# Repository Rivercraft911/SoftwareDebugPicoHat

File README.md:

# Software Debug Pico Hat

A simple breakout board for the Raspberry Pi Pico, designed for S-Band and UHF LORA modules. It also includes exposed gpio pins for connection to other boards within the Samwise avionics stack.

[View Schematic PDF](Plots/SoftwareDebugPicoHat.pdf)

## Power

//type this up later frfr

## Pinout

This board connects to a Raspberry Pi Pico and provides the following pinouts:

### Raspberry Pi Communication
| Pin | Function      | Pico Pin |
|-----|---------------|----------|
| 0   | RPI_TX        | GP0      |
| 1   | RPI_RX        | GP1      |
| 2   | RPI_ENABLE    | GP2      |
| 3   | RPI_RESET     | GP3      |

### ACDS Communication
| Pin | Function      | Pico Pin |
|-----|---------------|----------|
| 4   | ACDS_TX       | GP4      |
| 5   | ACDS_RX       | GP5      |

### S-Band Module (LORA1280F27-TCXO)
| Pin | Function      | Pico Pin |
|-----|---------------|----------|
| 8   | SBAND_RST     | GP8      |
| 9   | SBAND_BUSY    | GP9      |
| 10  | SBAND_TXEN    | GP10     |
| 11  | SBAND_RXEN    | GP11     |
| 12  | SBAND_MISO    | GP12     |
| 13  | SBAND_CS      | GP13     |
| 14  | SBAND_SCK     | GP14     |
| 15  | SBAND_MOSI    | GP15     |
| 20  | SBAND_D1      | GP20     |

### UHF LORA Module (RFM98PW)
| Pin | Function      | Pico Pin |
|-----|---------------|----------|
| 16  | UHF_MISO      | GP16     |
| 17  | UHF_CS        | GP17     |
| 18  | UHF_SCK       | GP18     |
| 19  | UHF_MOSI      | GP19     |
| 20  | UHF_RST       | GP21     |
| 28  | UHF_D0        | GP28     |

### Miscellaneous
| Pin | Function      | Pico Pin |
|-----|---------------|----------|
| 26  | NEOPIXEL      | GP26     |
| 6   | MISC          | GP6      |
| 7   | MISC          | GP7      |

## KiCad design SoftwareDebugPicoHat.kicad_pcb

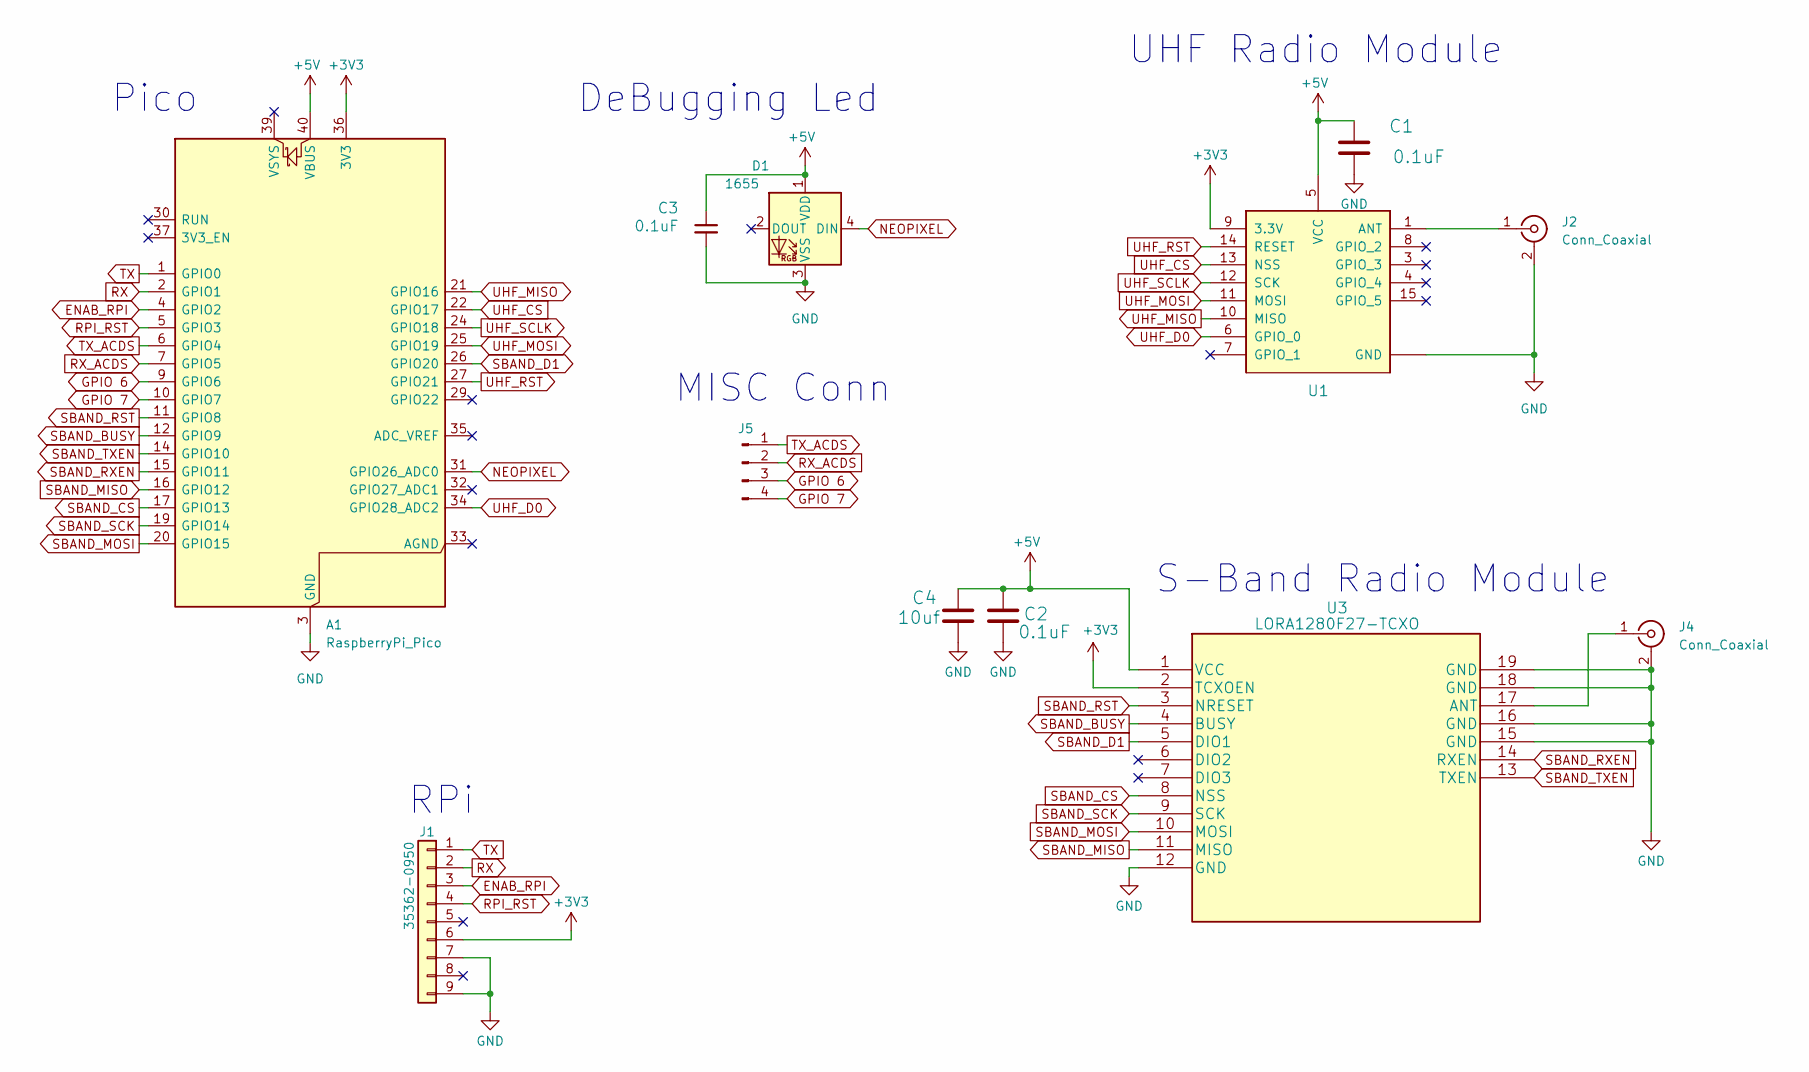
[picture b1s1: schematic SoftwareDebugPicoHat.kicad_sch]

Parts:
A1: RaspberryPi_Pico; RaspberryPi_Pico_Common_THT
C1, C2, C3: 0.1uF; C_0603_1608Metric
C4: 10uf; C_0603_1608Metric
D1: 1655; LED_WS2812B_PLCC4_5.0x5.0mm_P3.2mm; Manufacturer_Part_Number SK6812
J1: 35362-0950; Molex_35362-0950
J2, J4: Conn_Coaxial; SMA_Amphenol_901-144_horizontal
J5: Conn_01x04_Pin; PinHeader_1x04_P2.54mm_Vertical
U1: RFM98PW
U3: LORA1280F27-TCXO; LORA128XF27

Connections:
+3V3: A1.36 (3V3), J1.6, U1.9 (3.3V), U3.2 (TCXOEN)
+5V: A1.40 (VBUS), C1.1, C2.1, C3.1, C4.1, D1.1 (VDD), U1.5 (VCC), U3.1 (VCC)
ENAB_RPI: A1.4 (GPIO2), J1.3
GND: A1.3 (GND), A1.8 (GND), A1.13 (GND), A1.18 (GND), A1.23 (GND), A1.28 (GND), A1.38 (GND), C1.2, C2.2, C3.2, C4.2, D1.3 (VSS), J1.7, J1.9, J2.2 (Ext), J4.2 (Ext), U1.2 (GND), U1.16 (GND), U1.17 (GND), U3.12 (GND), U3.15 (GND), U3.16 (GND), U3.18 (GND), U3.19 (GND)
GPIO 6: A1.9 (GPIO6), J5.3
GPIO 7: A1.10 (GPIO7), J5.4
NEOPIXEL: A1.31 (GPIO26_ADC0), D1.4 (DIN)
unnamed: J2.1 (In), U1.1 (ANT)
unnamed: J4.1 (In), U3.17 (ANT)
RPI_RST: A1.5 (GPIO3), J1.4
RX: A1.2 (GPIO1), J1.2
RX_ACDS: A1.7 (GPIO5), J5.2
SBAND_BUSY: A1.12 (GPIO9), U3.4 (BUSY)
SBAND_CS: A1.17 (GPIO13), U3.8 (NSS)
SBAND_D1: A1.26 (GPIO20), U3.5 (DIO1)
SBAND_MISO: A1.16 (GPIO12), U3.11 (MISO)
SBAND_MOSI: A1.20 (GPIO15), U3.10 (MOSI)
SBAND_RST: A1.11 (GPIO8), U3.3 (NRESET)
SBAND_RXEN: A1.15 (GPIO11), U3.14 (RXEN)
SBAND_SCK: A1.19 (GPIO14), U3.9 (SCK)
SBAND_TXEN: A1.14 (GPIO10), U3.13 (TXEN)
TX: A1.1 (GPIO0), J1.1
TX_ACDS: A1.6 (GPIO4), J5.1
UHF_CS: A1.22 (GPIO17), U1.13 (NSS)
UHF_D0: A1.34 (GPIO28_ADC2), U1.6 (GPIO_0)
UHF_MISO: A1.21 (GPIO16), U1.10 (MISO)
UHF_MOSI: A1.25 (GPIO19), U1.11 (MOSI)
UHF_RST: A1.27 (GPIO21), U1.14 (RESET)
UHF_SCLK: A1.24 (GPIO18), U1.12 (SCK)

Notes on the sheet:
Pico
MISC Conn
RPi
UHF Radio Module
S-Band Radio Module
DeBugging Led

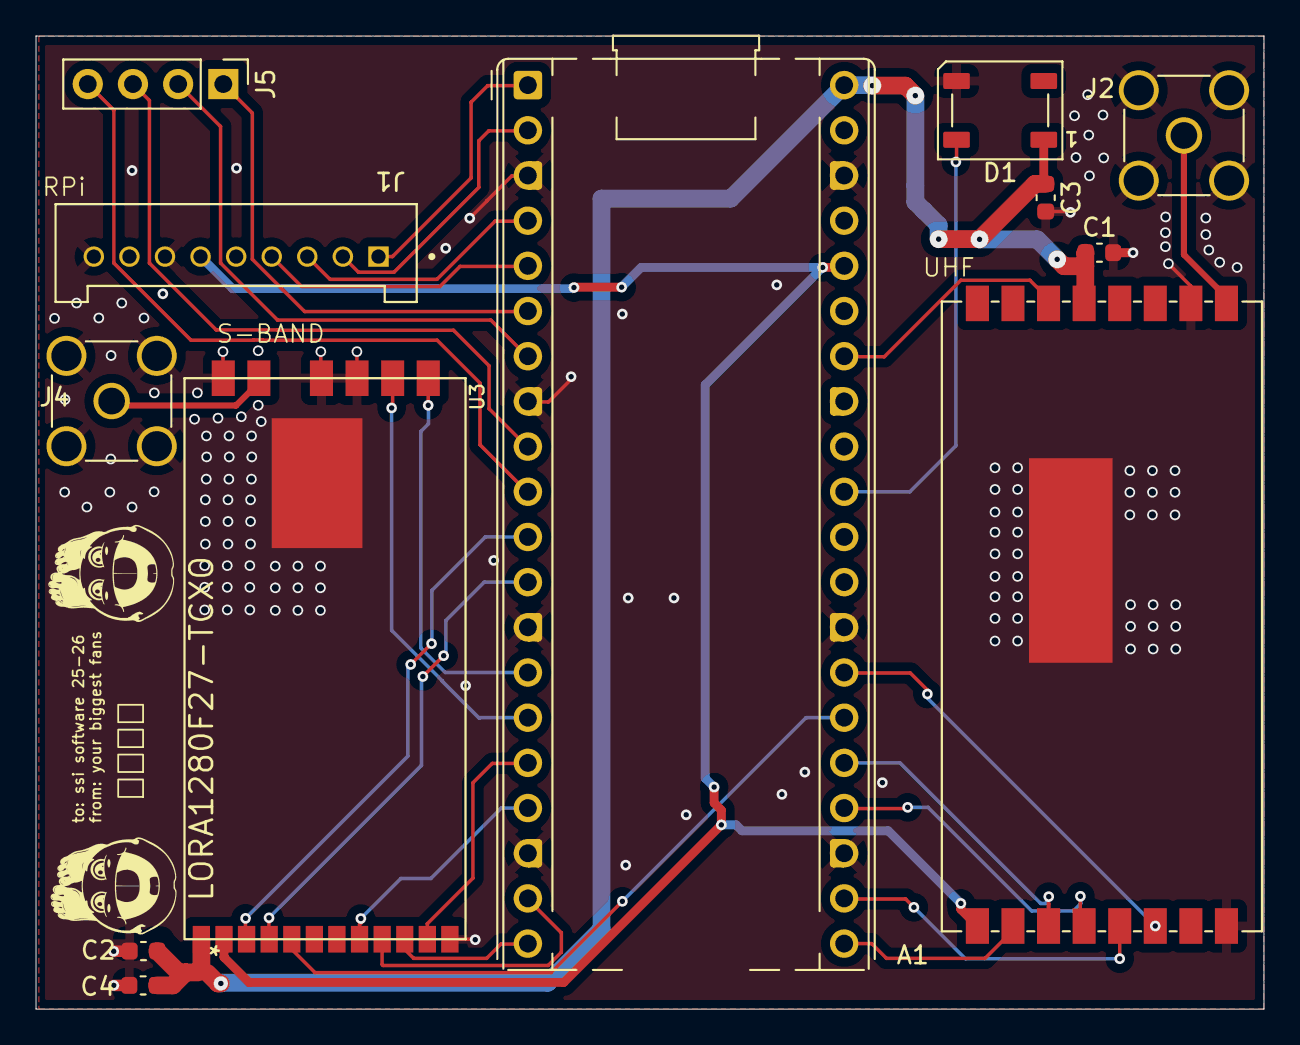
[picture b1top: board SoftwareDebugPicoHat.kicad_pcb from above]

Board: 4 copper layers, 69.0 x 54.7 mm, 12 parts (0 on the bottom side), 29 nets.

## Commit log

2026-01-27 Stuff
2026-01-31 Updated to throughhole pico
2026-01-31 Removed Prod File
2026-01-31 RELEASE: 1 ) Updated some component locations for better placement
2026-01-31 Closed FIle
2026-02-03 Added READ.me and fixed org sys
2026-02-03 Added Model numbers and closed files
2026-02-03 Updated READ.me to include the power stipulation
2026-02-16 Update UHF_RST pin mapping from GP20 to GP21
2026-02-24 Update power section in README
    Clarified power requirements for S-Band and UHF LoRa modules.
2026-02-24 Solving Samwise
2026-02-24 Fixed Scem
2026-02-27 Removed UBC and TCXO-EN Pullup resistor
2026-02-28 FIxed Caps
